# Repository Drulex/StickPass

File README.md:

# STICKPASS

## What is the StickPass project?
StickPass is a hardware password manager based on the ATTINY85 microcontroller. It allows the user to securely store his identities (username/password combinations) on a physical device and use them with the press of a button. At the moment it uses the V-USB library to implement USB functionality in software.

## Scope
The scope of the project is to develop a low cost integrated hardware password management solution. The project is realized as a final year electrical engineering project and the timeline is 12 weeks at about 9 hours of work per week.

## Why ATTINY85?
There are two obvious ways of going when thinking about the architecture of this project:

1. Use an IC with integrated USB.
2. Use a general purpose IC and a separate chip acting as USB bridge.

Yet I chose to explore a third more obscure option: Use a software implementation of the USB protocol.

The reasons for this decision are the following:
* V-USB if fully compliant with USB1.1.
* ATTINY85 is an extremely small package (8 pin DIP package). There are no ICs with integrated USB that are this small.
* Very cheap (~1.67$) compared to other ICs with USB integrated or compared to using two ICs.
* Hardware is greatly simplified as the IC is powered directly from USB VCC and does not require a single external component (not even oscillator).
* This project does not require a lot of CPU and memory resources nor does it need full speed USB protocol.
* AVR chips are very well documented and used in various projects in the online community.
* Need to go from nothing to "production ready" in less than 150 hours.

## Compiling the firmware
At the moment this was only tested on Linux. Cross platform support is coming.

#### Linux
The following packages are required in order to build the firmware:
* avr-libc
* arvdude
* binutils-avr
* gcc-avr

If you are not using the USBTINY programmer to flash your ATTINY85 modify line 6 of the Makefile to call your programmer.

To compile the project: ``` make hex ```

To flash the chip: ``` make flash ```

To flash the fuses: ``` make fuse ```

#### OSX
Coming soon.

#### Windows
Coming soon... or not.

## Compiling the user application
In order to use the user application (StickApp) you will need a recent version of:
* gcc
* libusb

To compile the app: ``` make app ```

## Using the StickApp

#### Device initialization
```./stickapp --init <unlock key> ```

This will initialize the device with the given unlock key. This key must be used to unlock the device any time it is plugged in the future!
When used on an already initialized device it will wipe the memory contents and reset the key.

#### Send credentials to device
```./stickapp --send <idName> <idUsername> <idPassword> ```
* idName: nickname associated with credential
* idUsername: username associated with credential
* idPassword: password associated with credential

#### Clearing the EEPROM
``` ./stickapp --clear ```
Will clear the memory contents and preserve the unlock key.

#### Using credentials
To use the device:

1. Plug in computer. The LED should light up and stay solid. This means the device is locked.
2. Unlock the device using the unlock key.
3. A pushbutton shortpress (lesser than 1 second) will display and iterate through available idNames.
4. A pushbutton long press (greater than 1 second) will inject the idUsername, the TAB character and the idPassword.

## Limitations
Some decisions were made to implement some features (most of them related to memory management) with limitations in order to satisfy the requirements, but at the same time decrease complexity and ultimately save some time. I am obviously aware that these implementations are suboptimal and I plan on fixing them as soon as the semester is done and time allows.

##### Current limitations on version 1.0:
1. Maximum of 8 credentials capacity as per scheme below:
   * idName: 10 bytes
   * idUsername: 32 bytes
   * idPassword: 21 bytes
2. Unlock key size is 7 bytes.
3. No mechanisms implemented to prevent EEPROM corruption. This means that if you remove power during an EEPROM write cycle your data WILL be corrupted.

## Next version
I already have some ideas for the next iteration the main ones being:

1. External memory chip with hardware encryption.
2. NFC support for 2 factor authentication.
3. Rotating knob for navigation.
4. Tiny OLED matrix display.

If you have suggestions contact me at alexandru@jora.ca I would love to get some feedback.

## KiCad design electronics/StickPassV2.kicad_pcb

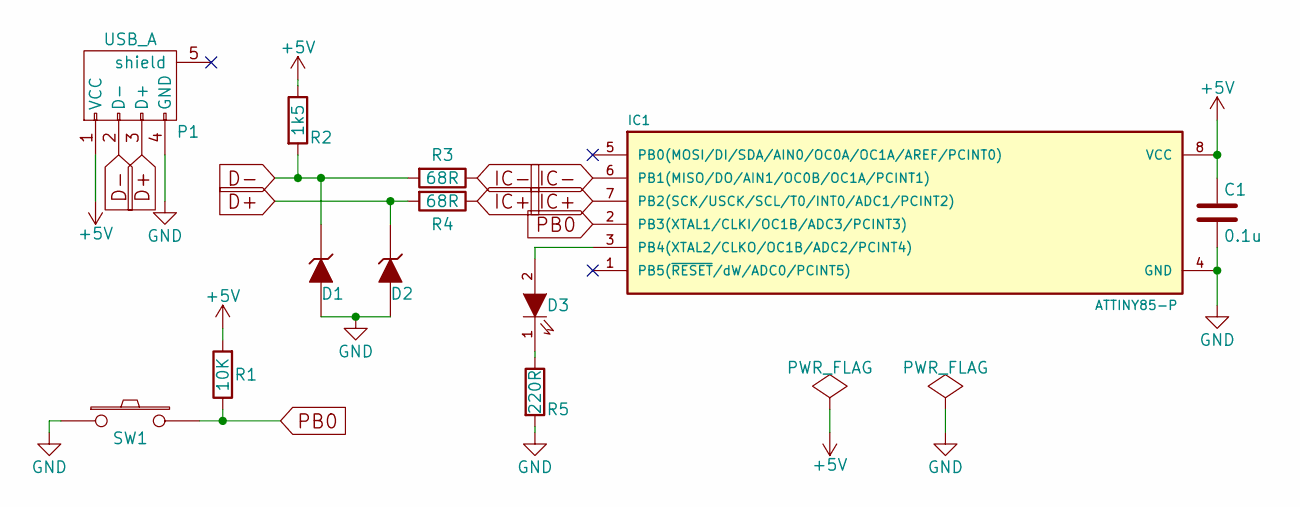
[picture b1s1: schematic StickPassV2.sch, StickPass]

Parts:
C1: 0.1u; Resistor_Horizontal_RM7mm
D1, D2: ZENER; Resistor_Horizontal_RM7mm
D3: LED; LED-5MM
IC1: ATTINY85-P; DIP-8_W7.62mm
P1: USB_A; usb_a_molex_48037-0001
R1: 10K; Resistor_Horizontal_RM10mm
R2: 1k5; Resistor_Horizontal_RM10mm
R3, R4: 68R; Resistor_Horizontal_RM7mm
R5: 220R; Resistor_Horizontal_RM10mm
SW1: SW_PUSH; SPST-4-PIN_6mm_thru

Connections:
+5V: C1.1, IC1.8 (VCC), P1.1 (VCC), R1.2, R2.1
D+: D2.1 (K), P1.3 (D+), R4.2
D-: D1.1 (K), P1.2 (D-), R2.2, R3.2
GND: C1.2, D1.2 (A), D2.2 (A), IC1.4 (GND), P1.4 (GND), R5.2, SW1.1
IC+: IC1.7 (PB2(SCK/USCK/SCL/T0/INT0/ADC1/PCINT2)), R4.1
IC-: IC1.6 (PB1(MISO/DO/AIN1/OC0B/OC1A/PCINT1)), R3.1
unnamed: D3.1 (K), R5.1
unnamed: D3.2 (A), IC1.3 (PB4(XTAL2/CLKO/OC1B/ADC2/PCINT4))
PB0: IC1.2 (PB3(XTAL1/CLKI/OC1B/ADC3/PCINT3)), R1.1, SW1.2

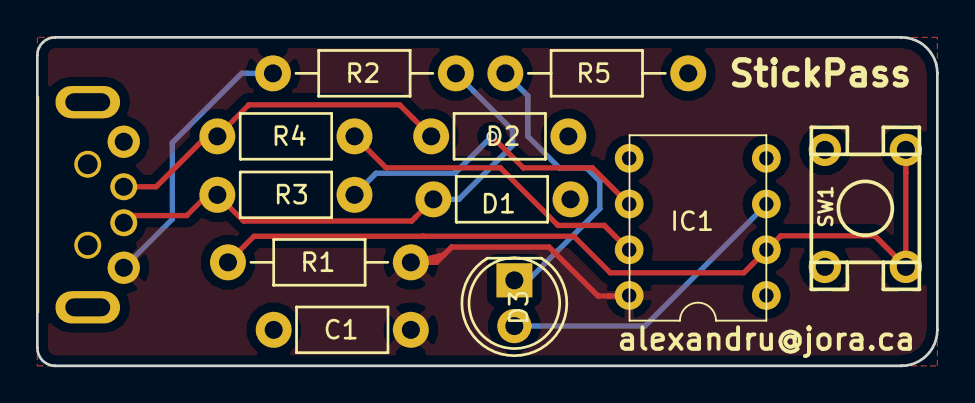
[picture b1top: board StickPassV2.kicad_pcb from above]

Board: 2 copper layers, 50.0 x 18.2 mm, 12 parts (0 on the bottom side), 9 nets.

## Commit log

2015-12-15 add reference documents
2015-12-16 organize documents
2015-12-16 add requirements document
2015-12-16 update requirements document
2016-01-21 Updated documentation
2016-01-26 Update gitignore
2016-01-26 Add V-USB firmware and documentation
2016-01-27 Starting to write Makefile.
2016-01-27 Improve base Makefile
2016-01-27 Modified Makefile as per sample found online.
2016-01-27 Add V-USB to project
2016-01-27 Add usbconfig.h
2016-01-27 Add test main.c.
2016-01-27 Remove unneeded stuff from VUSB project.
2016-01-28 Add Kicad electronic project files.
2016-01-28 Maintain a file with useful information.
2016-01-28 Modify the prototype usbconfig.h file to correspond to circuit.
2016-01-28 Remove unused defines from usbconfig header file.
2016-01-28 Fix weird type in usbconfig.h.
2016-01-29 Add some test code to flash LED via USB.
2016-01-29 Add oscillator calibration routine (created by cpldcpu).
2016-01-29 Modify usbconfig for testing purposes.
2016-01-29 Modify Makefile to add ability to flash fuses.
2016-01-29 Update gitignore.
2016-01-29 Start writing user app. Took usbGetStringAscii from V-USB's usbtool example project.
2016-01-31 Adding user application in its own folder.
2016-01-31 Adapting firmware for USB communications testing.
2016-01-31 Improve logging of user app.
2016-02-01 Updating gitignore.
2016-02-01 Remove static types as it is not needed.
2016-02-01 Testing reading and writing of EEPROM memory.
2016-02-01 Add todo list.
2016-02-01 Implement logic to send debug messages on debugFlag event.
2016-02-03 Starting some initial implementation of credentials module.
2016-02-03 Add some macros for constants.
2016-02-03 Write credentials to eeprom.
2016-02-04 Configuring V-USB to use interrupt endpoint 1.
2016-02-04 Writing credentials module.
2016-02-04 Restructure main.c to test interrupt in data transfer to host.
2016-02-04 Add interrupt in functionality to user app.
2016-02-04 Code cleanup.
2016-02-04 User app: display VID and PID in hex.
2016-02-04 Move led library to its own header file.
2016-02-04 Update gitignore and move some files.
2016-02-06 Code cleanup + added license.
2016-02-08 Debounce on switch press.
2016-02-13 Modify usbconfig.h in order to use device as HID.
2016-02-13 Add usbHidDescriptor for keyboard.
2016-02-13 Structure for keyboard report.
2016-02-13 Modify usbFunctionSetup to respond to proper HID requests on endpoint control 0.
2016-02-13 Add function to build report. For sake of simplicity suppor tonly chars between 'a' and 'z'.
2016-02-13 Modify usbFunctionWrite to control the LED.
2016-02-13 Change main logic to test HID functionality.
2016-02-13 Modify keyboard_report structure to handle one key at the time.
2016-02-13 Move some HID related stuff to its own module.
2016-02-13 Define pushbutton init.
2016-02-13 Modify Makefile to add hid module.
2016-02-18 Add dot and underscore to buildReport function.
2016-02-18 Write some functions to help testing credentials module.
2016-02-18 Test iterating through elements of ID_BLOCK and inject to host.
2016-02-18 Update planning spreadsheet.
2016-02-18 Update electronic circuit files.
2016-02-18 Cleanup documents.
2016-02-18 Add rapport d'étape.
2016-02-22 Fix bug in PB init!
2016-02-22 Setup timer1 to 100ms.
2016-02-22 Implement PB long press detection.
2016-02-22 Remove unused debug stuff.
2016-02-22 Remove unused stuff.
2016-02-22 Add timer1 routines in its own module.
2016-02-22 Modify Makefile to create timer1 object file.
2016-02-22 Add rapport d'etape files.
2016-02-22 Add support to turn LED ON or OFF from usbFunctionSetup.
2016-02-22 Change PB long delay to 1s instead of 1.5s.
2016-02-22 Switch back to the other VID/PID pair that supports control OUT requests.
2016-02-25 Implementing state machine to send ID_BLOCKS to device.
2016-02-26 Re-implement logic to send 8bytes chunks of data.
2016-02-26 Simplify code.
2016-02-26 Add some extra test data in app.
2016-02-26 Cleanup unused stuff from credentials module.
2016-02-26 Testing.
2016-02-27 Add support for tab and backspace keys.
2016-02-27 Initial implementation of id cycling.
2016-02-27 Add some test data.
2016-02-27 Semi working state of id cycling.
2016-02-27 Fix credentials module to not use global cred_t.
2016-02-27 Fix terrible bug in long PB detection. I don't even understand how it could have worked in the previous version of the code...
2016-02-27 Improved logic working with dummy data.
2016-02-28 Simplify getCredentialData function and save some RAM.
2016-02-28 Improve user app.
2016-02-28 Finish id cycling implementation.
2016-02-28 Adjust credentials module to resize idPassword to 21 bytes and free 8 bytes to use for calibration data in EEPROM.
2016-02-28 Implement EEPROM clearing and recover EEPROM data when cycling.
2016-02-29 Simplifying main module.
2016-02-29 Implementing device protection via key.
2016-02-29 Improve user app experience.
2016-03-02 Update electronic schematic and add gerber files.
2016-03-02 Add init functionality to user app.
2016-03-02 Modify clearEEPROM routine to preserve masterKey if wanted.
2016-03-02 Write function to retrieve master key from EEPROM.
2016-03-02 Write function to set master key in EEPROM memory.
2016-03-02 Add comments and cleanup credentials module.
2016-03-02 Implement init device functionality.
2016-03-03 Add error checking to user app.
2016-03-03 Add README.
2016-03-03 Move README to project root.
2016-03-03 Once again move README to project root dir.
2016-03-04 Update README.
2016-03-11 At EEPROM erase after 5 failed attempts at unlocking device.
2016-03-13 Cleanup
2016-04-03 Add GNU GPL v3 license.
2016-04-11 Fix a few issues in user app.
2016-04-13 Add archine as email server blocks .zip files.
